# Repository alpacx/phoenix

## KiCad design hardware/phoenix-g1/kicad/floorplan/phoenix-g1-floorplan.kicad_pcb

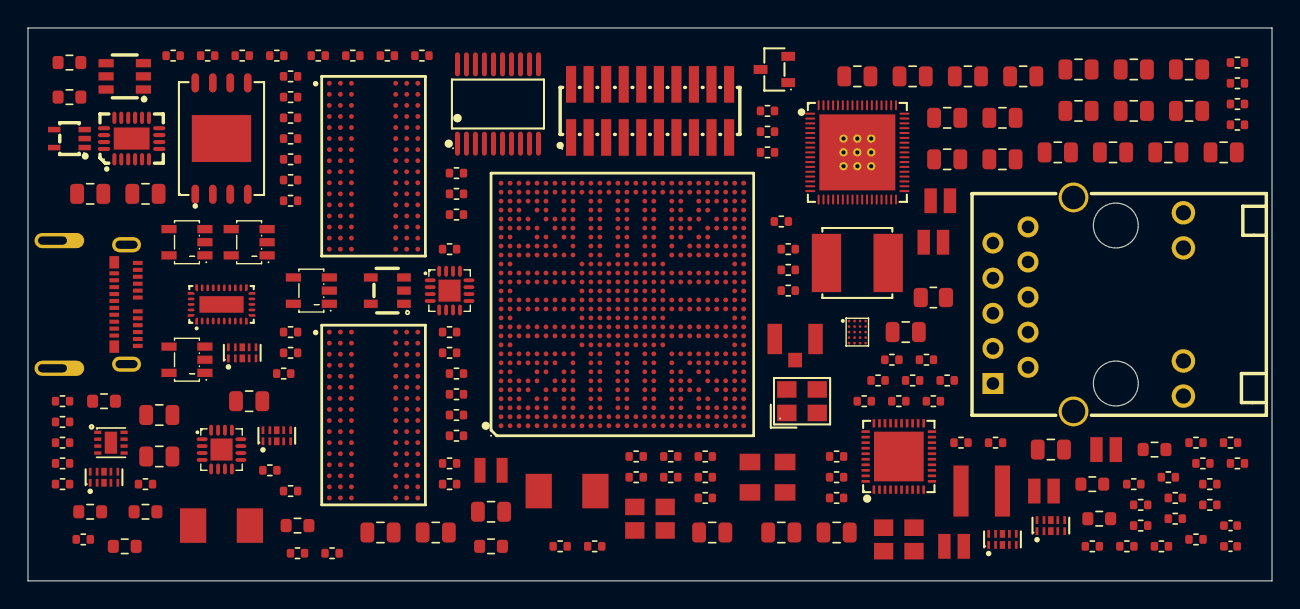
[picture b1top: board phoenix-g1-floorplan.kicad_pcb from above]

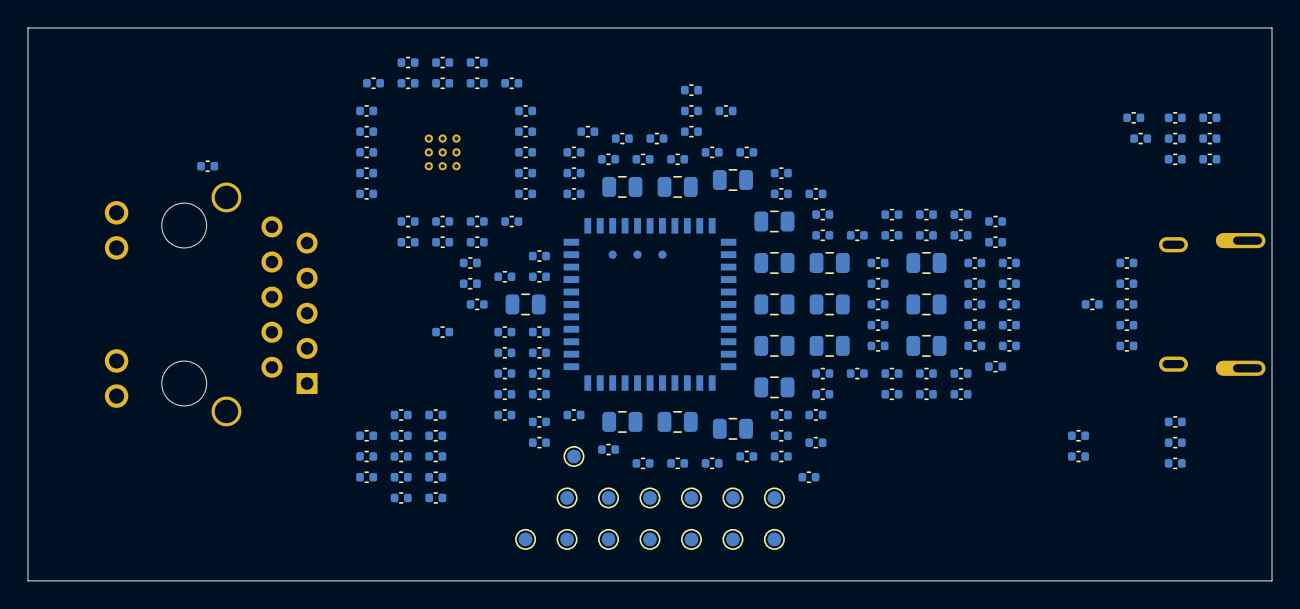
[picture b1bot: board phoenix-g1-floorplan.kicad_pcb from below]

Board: 6 copper layers, 90.0 x 40.0 mm, 354 parts (175 on the bottom side), 272 nets, no tracks yet.

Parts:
C401, C402, C1903: 1n / C0G; C_0402_1005Metric
C410, C411, C412, C451, C452, C454, C501, C512, C513, C514, C516, C517, C518, C522, C1103, C1104, C1105, C1106, C1107, C1401, C1503, C1811, C2007: 100n; C_0402_1005Metric
C413, C414, C415, C519, C1402: 1u; C_0402_1005Metric
C421, C422, C423, C424, C425, C431, C432, C433, C434, C435, C441, C442, C443, C444, C445, C1304, C1305, C1603, C1604, C1605, C1606, C1607, C1608, C1613, C1614, C1618, C1619, C1622, C1623, C2204: 22u / 10V; C_0805_2012Metric
C460, C461, C462, C463, C464, C465, C466, C467, C468, C469, C480, C481, C482, C483, C484, C485, C531, C1101, C1201, C1203, C1611, C1612, C1626, C1628, C1630, C1632, C1634, C1636, C1680, C1682, C1801, C1812, C2005: 1u / 10V; C_0402_1005Metric
C470, C1301, C1615, C1620, C1624, C1650, C1664, C1678, C2201: 10u / 10V; C_0805_2012Metric
C511, C515: 4.7u; C_0402_1005Metric
C520, C521, C1501, C1502: 20p C0G / tune; C_0402_1005Metric
C601, C602, C603, C604, C605: 100n / 16V X7R; C_0402_1005Metric
C606: 100n / 10V X7R; C_0402_1005Metric
C1001, C1002, C1011, C1012, C1013, C1014: 22u / 10V X5R; C_0805_2012Metric
C1020: 1u / 10V X5R; C_0402_1005Metric
C1102, C1802: 2.2u / 10V; C_0402_1005Metric
C1202: 22n / 10V; C_0402_1005Metric
C1302, C1601, C1609, C1616, C1621, C1625, C1627, C1629, C1631, C1633, C1635, C1637, C1638, C1639, C1640, C1641, C1642, C1643, C1644, C1645, C1646, C1647, C1651, C1652, C1653, C1654, C1655, C1656, C1657, C1658, C1659, C1660, C1661, C1662, C1665, C1666, C1667, C1668, C1669, C1670, C1671, C1672, C1673, C1674, C1675, C1676, C1679, C1681, C1683: 100n / 10V; C_0402_1005Metric
C1303: 10n / 10V; C_0402_1005Metric
C1602, C1610, C1617, C1648, C1649, C1663, C1677: 4.7u / 10V; C_0402_1005Metric
C1901, C1902: 1u / 25V X7R; C_0805_2012Metric
C2001: 22u / 6.3V; C_0805_2012Metric
C2002, C2006, C2202: 100n / 16V; C_0402_1005Metric
C2003: 4.7u / 6.3V; C_0805_2012Metric
C2004: 4.7u / 6.3V; C_0402_1005Metric
C2008, C2009: 8p C0G; C_0402_1005Metric
C2203: 1n / 10V; C_0402_1005Metric
FB2001: 100R @100MHz / 4A; R_0805_2012Metric
J1: 2012670005; USB_C_Molex_2012670005
J2: HR911130A; RJ45-TH_HR911130A
J3: PZ127-2-10-S; HDR-SMD_PZ127-2-10-S
J2001: U.FL-R-SMT-1; Hirose_UFL_R_SMT_1_80
L401, L402, L403, L404, L405: 470nH; L_APH201610
L501: 2.2uH DCR39m max; L_ANR4030
L1001: 240nH - candidate; IND-SMD_L5.0-W5.0-PRS5020-330MT
L1301, L2201: 2.2uH DCR35m max; L_APH0518
L2001: 2.2uH / 2.4A Isat at 20C; Murata_DFE201610E
Q1: MMBT3904-C20526; SOT-23-3_L2.9-W1.3-P1.90-LS2.4-BR
R201, R301: 240R 1%; R_0402_1005Metric
R401, R402: 1k 1%; R_0402_1005Metric
R410: 180k 1%; R_0402_1005Metric
R411, R1505, R2203: 100k 1%; R_0402_1005Metric
R412, R413, R516, R1402, R1403, R1404, R1405, R1504, R2002: 10k; R_0402_1005Metric
R414, R415, R501, R502, R503, R504, R505, R506, R507, R508, R509, R510, R511, R512, R515, R1401, R1501, R2003: 22R; R_0402_1005Metric
R416, R417: 2.2k; R_0402_1005Metric
R421, R422, R424, R2004: 100R; R_0402_1005Metric
R431: 105k 0.1%; R_0603_1608Metric
R432: 120k 0.1%; R_0603_1608Metric
R513: 2.49k 1%; R_0402_1005Metric
R514: 1.8k; R_0402_1005Metric
R521, R522, R523, R524, R525, R526, R527, R528, R529, R2101, R2102: 4.7k; R_0402_1005Metric
R530: 0R - power link; R_0402_1005Metric
R601, R605, R606: 300k 0.1% 25ppm; R_0603_1608Metric
R602, R603, R604: 200k 1%; R_0402_1005Metric
R1001: 100R 1%; R_0402_1005Metric
R1002: 51k 1%; R_0402_1005Metric
R1101, R1103, R1202, R1301, R1804, R2201: 100k; R_0402_1005Metric
R1102, R1802, R1811, R1812, R1813, R1814, R1815, R2010, R2011, R2012, R2013, R2014, R2103, R2104: 47k; R_0402_1005Metric
R1201: 806R 1%; R_0603_1608Metric
R1502: 1M; R_0402_1005Metric
R1503: 120R 1%; R_0402_1005Metric
R1506: 1M 1%; R_0402_1005Metric
R1507: 0R; R_0402_1005Metric
R1601, R1602: 0R supply link; R_0402_1005Metric
R1801: 1k; R_0402_1005Metric
R1803: 180R 1%; R_0603_1608Metric
R1901: 35.7k 0.1% 25ppm; R_0603_1608Metric
R1902, R1904: 10k 0.1% 25ppm; R_0402_1005Metric
R1903: 47.5k 0.1% 25ppm; R_0603_1608Metric
R1905: 33.2k 1%; R_0603_1608Metric
R2001: 0R RF tuning; R_0402_1005Metric
R2202: 348k 1%; R_0603_1608Metric
TP1: GND; TestPoint_Pad_D1.0mm
TP2: VBUS_RAW; TestPoint_Pad_D1.0mm
TP3: +5V_MAIN; TestPoint_Pad_D1.0mm
TP4: +3V3_SYS; TestPoint_Pad_D1.0mm
TP5: +3V3_PMU; TestPoint_Pad_D1.0mm
TP6: +3V3_IO; TestPoint_Pad_D1.0mm
TP7: +1V5_DDR; TestPoint_Pad_D1.0mm
TP8: VDD_CPU; TestPoint_Pad_D1.0mm
TP9: RESET_N; TestPoint_Pad_D1.0mm
TP10: RECOVERY_ADC; TestPoint_Pad_D1.0mm
TP11: DEBUG_RX; TestPoint_Pad_D1.0mm
TP12: DEBUG_TX; TestPoint_Pad_D1.0mm
TP13: USB_POWER_FAULT_N; TestPoint_Pad_D1.0mm
TP14: SYS_3V3_PG; TestPoint_Pad_D1.0mm
U1: RK3568; BGA-636_L19.0-W19.0-P0.65-BL
U2, U3: H5TQ2G63GFR-TEC; TFBGA-96_L13.0-W7.5-R16-C6-P0.80-TL
U4: RK809-5; QFN-68_L7.0-W7.0-P0.35-BL-EP5.5
U5: RTL8211F-CG; WQFN-40_L5.0-W5.0-P0.4-BL-EP
U6: HD3SS3220IRNHR; WQFN-30_L4.5-W2.5-P0.4-BL-EP
U7, U8, U9: TPD4EUSB30DQAR; USON-10_L2.5-W1.0-P0.50-BL
U10: RK860-0; WLCSP-20_L2.0-W1.6-R5-C4-P0.40-TL
U11: TLV75533PDBVR; SOT-23-5_L3.0-W1.7-P0.95-LS2.8-BR
U12: TPS3808G33DBVR; SOT-23-6_L2.9-W1.6-P0.95-LS2.8-BR
U13, U16: SN74LVC1G04DBVR; SOT-23-5_L3.0-W1.7-P0.95-LS2.8-BR
U14: SN74LVC1G02DCKR; SC-70-5_L2.1-W1.3-P0.65-LS2.1-BR
U15: TPS259531DSGR; WSON-8_L2.0-W2.0-P0.50-TL-EP
U17: TPS62132RGTR; VQFN-16_L3.0-W3.0-P0.50-TL-EP
U18: W25Q256JVEIQTR; WSON-8_L8.0-W6.10-P1.27-BL-EP
U19: SN74LVC1G08DBVR; SOT-23-5_L3.0-W1.7-P0.95-LS2.8-BR
U20: TPS7A2030PDBVR; TSOT-23-5_L2.9-W1.6-P0.95-LS2.8-BR
U21: SN74LVC541APWR_C113281; TSSOP-20_L6.5-W4.4-P0.65-LS6.4-BL
U22, U23: TPD4E05U06DQAR; USON-10_L2.5-W1.0-P0.50-BL
U24: TPS25940ARVCR; WQFN-20_L4.0-W3.0-P0.50-BL-EP
U25: AP6256; AP6256_12x12_P0.9
U26: TPS62130RGTR; VQFN-16_L3.0-W3.0-P0.50-TL-EP
Y1: 24MHz CL12pF ESR40R; Crystal_3225_JWT
Y501: 25MHz CL12pF; Crystal_3225_YXC
Y2001: OVETDLJANF-32.768KHZ; Taitien_OV_5032
Y2002: X1E0000210877; CRYSTAL-SMD_4P-L3.2-W2.5-BL

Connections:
+1V0_PHY: C511.1, C512.1, C513.1, C514.1, C522.1, L501.2, U5.3, U5.8, U5.21, U5.38
+1V5_DDR: C433.1, C443.1, C1646.1, C1647.1, C1648.1, C1649.1, C1650.1, C1651.1, C1652.1, C1653.1, C1654.1, C1655.1, C1656.1, C1657.1, C1658.1, C1659.1, C1660.1, C1661.1, C1662.1, C1663.1, C1664.1, C1665.1, C1666.1, C1667.1, C1668.1, C1669.1, C1670.1, C1671.1, C1672.1, C1673.1, C1674.1, C1675.1, C1676.1, C1677.1, C1678.1, L403.2, R401.1, R431.1, TP7.1, U1.H9, U1.H11, U1.H12, U1.H14, U1.H15, U1.J9, U1.J11, U1.J12, U1.J14, U1.K10, U1.L9, U1.L10, U1.M9, U1.M10, U2.A1, U2.A8, U2.B2, U2.C1, U2.C9, U2.D2, U2.D9, U2.E9, U2.F1, U2.G7, U2.H2, U2.H9, U2.K2, U2.K8, U2.N1, U2.N9, U2.R1, U2.R9, U3.A1, U3.A8, U3.B2, U3.C1, U3.C9, U3.D2, U3.D9, U3.E9, U3.F1, U3.G7, U3.H2, U3.H9, U3.K2, U3.K8, U3.N1, U3.N9, U3.R1, U3.R9, U4.26
+1V8_SYS: C435.1, C445.1, L405.2, U4.59
+3V0_LCD: C1802.1, C1811.1, C1812.1, U20.5, U21.20
+3V3_AON: C606.1, C1102.1, C1103.1, C1104.1, C1105.1, C1106.1, C1107.1, R602.1, R603.1, R604.1, R1101.1, R1202.2, U6.8, U11.5, U12.3, U12.5, U12.6, U13.5, U14.5, U16.5, U19.5
+3V3_IO: C470.1, C1401.1, C1402.1, C1627.1, C1628.1, C1637.1, C1638.1, C1639.1, C1640.1, C1641.1, C1683.1, C2004.1, C2005.1, C2006.1, C2007.1, J3.1, R530.1, R1402.2, R1403.2, R1404.2, R1505.1, R1804.1, R1815.2, R2010.2, R2011.2, R2012.2, R2013.2, R2014.2, R2101.2, R2102.2, TP6.1, U1.H18, U1.J21, U1.L22, U1.M23, U1.R9, U1.U9, U4.55, U18.8, U20.3, U25.22, Y2001.1, Y2001.4
+3V3_PHY: C515.1, C516.1, C517.1, C518.1, C519.1, R514.2, R521.2, R525.2, R526.2, R527.2, R530.2, U5.11, U5.28, U5.29, U5.40
+3V3_PMU: C465.1, C1625.1, C1626.1, R412.1, R413.1, R416.1, R417.1, R1002.1, R2103.2, R2104.2, TP5.1, U1.W19, U1.Y20, U4.31
+3V3_SD: C469.1, U4.58
+3V3_SYS: C421.1, C422.1, C423.1, C424.1, C425.1, C480.1, C481.1, C482.1, C483.1, C484.1, C485.1, C1304.1, C1305.1, L1301.2, R410.1, R1301.2, TP4.1, U4.4, U4.10, U4.11, U4.22, U4.24, U4.30, U4.33, U4.45, U4.54, U4.57, U4.66, U17.14
+3V58_WIFI: C2204.1, FB2001.1, L2201.2, R2201.2, R2202.1, U26.14
+5V_MAIN: C1001.1, C1002.1, C1203.1, C1301.1, C1302.1, C1801.1, C2201.1, C2202.1, J3.2, R1803.1, TP3.1, U10.D1, U10.D2, U10.E1, U10.E2, U15.5, U17.10, U17.11, U17.12, U20.1, U26.10, U26.11, U26.12, U26.13
AON_READY: R1101.2, U12.1, U13.2, U19.2
CC_OUT1_N: R603.2, U6.25, U14.1
CC_OUT2_N: R604.2, U6.26, U14.2
CC_VBUS_SENSE: R606.2, U6.5
CC_VBUS_SERIES_1: R601.2, R605.1
CC_VBUS_SERIES_2: R605.2, R606.1
CHASSIS: J2.P10, J2.SHIELD0, J2.SHIELD1
CPU_BUCK_EN: R1002.2, U10.A2
CPU_SW: L1001.1, U10.D3, U10.D4, U10.E3, U10.E4
DDR3_A0: U1.E4, U2.N3, U3.N3
DDR3_A1: U1.E11, U2.P7, U3.P7
DDR3_A2: U1.F5, U2.P3, U3.P3
DDR3_A3: U1.F4, U2.N2, U3.N2
DDR3_A4: U1.B1, U2.P8, U3.P8
DDR3_A5: U1.A5, U2.P2, U3.P2
DDR3_A6: U1.C1, U2.R8, U3.R8
DDR3_A7: U1.C2, U2.R2, U3.R2
DDR3_A8: U1.A8, U2.T8, U3.T8
DDR3_A9: U1.B6, U2.R3, U3.R3
DDR3_A10: U1.D6, U2.L7, U3.L7
DDR3_A11: U1.B7, U2.R7, U3.R7
DDR3_A12: U1.E9, U2.N7, U3.N7
DDR3_A13: U1.A7, U2.T3, U3.T3
DDR3_BA0: U1.F7, U2.M2, U3.M2
DDR3_BA1: U1.D9, U2.N8, U3.N8
DDR3_BA2: U1.C4, U2.M3, U3.M3
DDR3_CASN: U1.E6, U2.K3, U3.K3
DDR3_CKE: U1.B3, U2.K9, U3.K9
DDR3_CLKN: U1.A4, U2.K7, U3.K7
DDR3_CLKP: U1.B4, U2.J7, U3.J7
DDR3_CS0N: U1.D8, U2.L2, U3.L2
DDR3_DM0: U1.H5, U2.E7
DDR3_DM1: U1.J4, U2.D3
DDR3_DM2: U1.D14, U3.E7
DDR3_DM3: U1.E17, U3.D3
DDR3_DQ0: U1.F2, U2.E3
DDR3_DQ1: U1.E1, U2.F7
DDR3_DQ2: U1.E2, U2.F2
DDR3_DQ3: U1.D1, U2.F8
DDR3_DQ4: U1.J1, U2.H3
DDR3_DQ5: U1.J2, U2.H8
DDR3_DQ6: U1.H1, U2.G2
DDR3_DQ7: U1.H4, U2.H7
DDR3_DQ8: U1.M1, U2.D7
DDR3_DQ9: U1.N2, U2.C3
DDR3_DQ10: U1.L7, U2.C8
DDR3_DQ11: U1.L6, U2.C2
DDR3_DQ12: U1.K2, U2.A7
DDR3_DQ13: U1.J6, U2.A2
DDR3_DQ14: U1.J7, U2.B8
DDR3_DQ15: U1.L4, U2.A3
DDR3_DQ16: U1.B10, U3.E3
DDR3_DQ17: U1.A9, U3.F7
DDR3_DQ18: U1.D12, U3.F2
DDR3_DQ19: U1.E12, U3.F8
DDR3_DQ20: U1.A12, U3.H3
DDR3_DQ21: U1.D15, U3.H8
DDR3_DQ22: U1.E15, U3.G2
DDR3_DQ23: U1.E14, U3.H7
DDR3_DQ24: U1.A16, U3.D7
DDR3_DQ25: U1.B17, U3.C3
DDR3_DQ26: U1.A17, U3.C8
DDR3_DQ27: U1.B18, U3.C2
DDR3_DQ28: U1.B13, U3.A7
DDR3_DQ29: U1.A13, U3.A2
DDR3_DQ30: U1.D17, U3.B8
DDR3_DQ31: U1.B14, U3.A3
DDR3_DQS0N: U1.G2, U2.G3
DDR3_DQS0P: U1.G1, U2.F3
DDR3_DQS1N: U1.L1, U2.B7
DDR3_DQS1P: U1.L2, U2.C7
DDR3_DQS2N: U1.B11, U3.G3
DDR3_DQS2P: U1.A11, U3.F3
DDR3_DQS3N: U1.A15, U3.B7
DDR3_DQS3P: U1.B15, U3.C7
DDR3_ODT0: U1.E8, U2.K1, U3.K1
DDR3_RASN: U1.D5, U2.J3, U3.J3
DDR3_RESETN: U1.F11, U2.T2, U3.T2
DDR3_WEN: U1.F8, U2.L3, U3.L3
DDR_FB: R431.2, R432.1, U4.27
DDR_RZQ: R1503.1, U1.H7
DDR_VREFCA: C401.1, R401.2, R402.1, U2.M8, U3.M8
DDR_VREFDQ: C402.1, U1.P8, U2.H1, U3.H1
DEBUG_RX: TP11.1, U1.AC20
DEBUG_TX: TP12.1, U1.AH24
ETH_CENTER_TAP: C531.1, J2.P1
ETH_MDC: U1.U5, U5.13
ETH_MDI0_N: J2.P3, U5.2, U22.2
ETH_MDI0_P: J2.P2, U5.1, U22.1
ETH_MDI1_N: J2.P7, U5.5, U22.5
ETH_MDI1_P: J2.P4, U5.4, U22.4
ETH_MDI2_N: J2.P6, U5.7, U23.2
ETH_MDI2_P: J2.P5, U5.6, U23.1
ETH_MDI3_N: J2.P9, U5.10, U23.5
ETH_MDI3_P: J2.P8, U5.9, U23.4
ETH_MDIO: R514.1, U1.U4, U5.14
ETH_RESET_GPIO_N: R515.1, U1.AE26
ETH_RXCLK: R512.1, U1.Y3
ETH_RXD0: R507.1, U1.W1
ETH_RXD1: R508.1, U1.V7
ETH_RXD2: R509.1, U1.AA2
ETH_RXD3: R510.1, U1.Y4
ETH_RXDV_CRS: R511.1, U1.V2
ETH_TXCLK: R506.1, U1.AA3
ETH_TXD0: R501.1, U1.Y2
ETH_TXD1: R502.1, U1.Y1
ETH_TXD2: R503.1, U1.Y6
ETH_TXD3: R504.1, U1.Y5
ETH_TXEN: R505.1, U1.W2
EXP_GPIO0: J3.12, U1.F27
EXP_GPIO1: J3.14, U1.U2
EXP_GPIO2: J3.16, U1.V4
EXP_GPIO3: J3.18, U1.V1
EXP_I2C_SCL: J3.5, R2102.1, U1.V5
EXP_I2C_SDA: J3.3, R2101.1, U1.V6
EXP_SPI_CLK: J3.7, U1.AC22
EXP_SPI_CS0_N: J3.13, R2103.1, U1.AD20
EXP_SPI_CS1_N: J3.15, R2104.1, U1.AD21
EXP_SPI_MISO: J3.11, U1.AC21
EXP_SPI_MOSI: J3.9, U1.AA20
EXP_UART_RX: J3.19, U1.F28
EXP_UART_TX: J3.17, U1.G27
FLASH_CLK: R1401.2, U18.6
FLASH_VOL_SEL: R1405.1, U1.AG25
FSPI_CLK: R1401.1, U1.A22
FSPI_CS_N: R1402.1, U1.C23, U18.1
FSPI_D0: U1.C24, U18.5
FSPI_D1: U1.D23, U18.2
FSPI_D2: R1403.1, U1.F20, U18.3
FSPI_D3: R1404.1, U1.A27, U18.7
GND: C401.2, C402.2, C410.2, C411.2, C412.2, C413.2, C414.2, C415.2, C421.2, C422.2, C423.2, C424.2, C425.2, C431.2, C432.2, C433.2, C434.2, C435.2, C441.2, C442.2, C443.2, C444.2, C445.2, C460.2, C461.2, C462.2, C463.2, C464.2, C465.2, C466.2, C467.2, C468.2, C469.2, C470.2, C480.2, C481.2, C482.2, C483.2, C484.2, C485.2, C501.2, C511.2, C512.2, C513.2, C514.2, C515.2, C516.2, C517.2, C518.2, C519.2, C520.2, C521.2, C522.2, C531.2, C605.2, C606.2, C1001.2, C1002.2, C1011.2, C1012.2, C1013.2, C1014.2, C1101.2, C1102.2, C1103.2, C1104.2, C1105.2, C1106.2, C1107.2, C1201.2, C1202.2, C1203.2, C1301.2, C1302.2, C1303.2, C1304.2, C1305.2, C1401.2, C1402.2, C1501.2, C1502.2, C1503.2, C1601.2, C1602.2, C1603.2, C1604.2, C1605.2, C1606.2, C1607.2, C1608.2, C1609.2, C1610.2, C1611.2, C1612.2, C1613.2, C1614.2, C1615.2, C1616.2, C1617.2, C1618.2, C1619.2, C1620.2, C1621.2, C1622.2, C1623.2, C1624.2, C1625.2, C1626.2, C1627.2, C1628.2, C1629.2, C1630.2, C1631.2, C1632.2, C1633.2, C1634.2, C1635.2, C1636.2, C1637.2, C1638.2, C1639.2, C1640.2, C1641.2, C1642.2, C1643.2, C1644.2, C1645.2, C1646.2, C1647.2, C1648.2, C1649.2, C1650.2, C1651.2, C1652.2, C1653.2, C1654.2, C1655.2, C1656.2, C1657.2, C1658.2, C1659.2, C1660.2, C1661.2, C1662.2, C1663.2, C1664.2, C1665.2, C1666.2, C1667.2, C1668.2, C1669.2, C1670.2, C1671.2, C1672.2, C1673.2, C1674.2, C1675.2, C1676.2, C1677.2, C1678.2, C1679.2, C1680.2, C1681.2, C1682.2, C1683.2, C1801.2, C1802.2, C1811.2, C1812.2, C1901.2, C1902.2, C1903.2, C2001.2, C2002.2, C2003.2, C2004.2, C2005.2, C2006.2, C2007.2, C2008.2, C2009.2, C2201.2, C2202.2, C2203.2, C2204.2, J1.A1, J1.A12, J1.B1, J1.B12, J3.4, J3.6, J3.8, J3.10, J3.20, J2001.2, J2001.3, Q1.2, R201.2, R301.2, R402.2, R411.2, R432.2, R513.2, R516.2, R522.2, R523.2, R524.2, R528.2, R529.2, R1102.2, R1103.2, R1201.2, R1405.2, R1503.2, R1506.2, R1802.2, R1804.2, R1811.2, R1812.2, R1813.2, R1814.2, R1902.2, R1904.2, R1905.2, R2002.2, R2203.2, TP1.1, U1.A1, U1.A3, U1.A6, U1.A10, U1.A14, U1.A18, U1.A28, U1.AA4, U1.AA9, U1.AA12, U1.AA14, U1.AA15, U1.AA17, U1.AA23, U1.AA24, U1.AA25, U1.AA26, U1.AB2, U1.AB6, U1.AB11, U1.AB12, U1.AB14, U1.AB15, U1.AB17, U1.AB24, U1.AC9, U1.AC11, U1.AC12, U1.AC15, U1.AC18, U1.AC25, U1.AC26, U1.AD3, U1.AD26, U1.AE6, U1.AE14, U1.AE17, U1.AE20, U1.AE21, U1.AE27, U1.AE28, U1.AF3, U1.AF9, U1.AF11, U1.AF12, U1.AF14, U1.AF15, U1.AF17, U1.AF18, U1.AF20, U1.AF21, U1.AF26, U1.AG5, U1.AG18, U1.AH1, U1.AH8, U1.AH18, U1.AH23, U1.AH28, U1.B5, U1.B9, U1.B12, U1.B16, U1.B23, U1.B26, U1.C3, U1.C6, U1.C8, U1.C9, U1.C11, U1.C12, U1.C14, U1.C15, U1.C17, U1.C18, U1.C25, U1.D2, U1.D3, U1.D11, U1.D28, U1.E3, U1.E7, U1.F1, U1.F3, U1.F9, U1.F12, U1.F14, U1.F15, U1.F17, U1.G5, U1.G6, U1.G8, U1.G9, U1.G11, U1.G12, U1.G14, U1.G15, U1.G17, U1.G18, U1.G24, U1.H2, U1.H3, U1.H6, U1.J3, U1.J5, U1.J8, U1.J17, U1.J18, U1.J20, U1.J22, U1.J26, U1.J27, U1.K1, U1.K11, U1.K12, U1.K13, U1.K14, U1.K19, U1.L3, U1.L5, U1.L8, U1.L11, U1.L13, U1.L14, U1.L19, U1.L20, U1.L21, U1.L24, U1.L26, U1.M2, U1.M3, U1.M6, U1.M8, U1.M11, U1.M13, U1.M14, U1.M16, U1.M18, U1.M20, U1.M21, U1.M22, U1.M26, U1.N1, U1.N11, U1.N12, U1.N14, U1.N15, U1.N17, U1.N18, U1.N28, U1.P3, U1.P6, U1.P9, U1.P10, U1.P12, U1.P14, U1.P15, U1.P17, U1.P21, U1.P26, U1.R3, U1.R6, U1.R8, U1.R10, U1.R11, U1.R14, U1.R15, U1.R17, U1.R18, U1.R19, U1.R23, U1.R26, U1.T10, U1.T11, U1.T14, U1.T15, U1.T17, U1.T18, U1.T19, U1.U1, U1.U6, U1.U7, U1.U8, U1.U10, U1.U14, U1.U15, U1.U16, U1.U17, U1.U18, U1.U20, U1.U21, U1.U22, U1.U23, U1.U26, U1.V3, U1.V8, U1.V9, U1.V13, U1.V14, U1.V15, U1.V16, U1.V17, U1.V18, U1.V20, U1.V22, U1.V23, U1.V26, U1.W10, U1.W11, U1.W12, U1.W13, U1.W14, U1.W15, U1.W16, U1.W17, U1.W18, U1.Y8, U1.Y9, U1.Y11, U1.Y12, U1.Y14, U1.Y15, U1.Y17, U1.Y18, U1.Y23, U1.Y24, U1.Y25, U1.Y26, U2.A9, U2.B1, U2.B3, U2.B9, U2.D1, U2.D8, U2.E1, U2.E2, U2.E8, U2.F9, U2.G1, U2.G8, U2.G9, U2.J2, U2.J8, U2.M1, U2.M9, U2.P1, U2.P9, U2.T1, U2.T9, U3.A9, U3.B1, U3.B3, U3.B9, U3.D1, U3.D8, U3.E1, U3.E2, U3.E8, U3.F9, U3.G1, U3.G8, U3.G9, U3.J2, U3.J8, U3.M1, U3.M9, U3.P1, U3.P9, U3.T1, U3.T9, U4.14, U4.15, U4.16, U4.17, U4.19, U4.40, U4.47, U4.56, U4.62, U4.63, U4.69, U5.41, U6.3, U6.4, U6.13, U6.28, U6.31, U7.3, U7.8, U8.3, U8.8, U9.3, U9.8, U10.B2, U10.B3, U10.B4, U10.C1, U10.C2, U10.C3, U10.C4, U11.2, U12.2, U13.3, U14.3, U15.8, U15.9, U16.3, U17.5, U17.6, U17.7, U17.8, U17.15, U17.16, U17.17, U18.4, U18.9, U19.3, U20.2, U21.1, U21.7, U21.8, U21.9, U21.10, U21.19, U22.3, U22.8, U23.3, U23.8, U24.1, U24.3, U24.16, U24.21, U25.1, U25.3, U25.6, U25.20, U25.26, U25.27, U25.28, U25.29, U25.31, U25.33, U25.34, U25.36, U25.43, U25.44, U26.6, U26.7, U26.8, U26.15, U26.16, U26.17, Y1.2, Y1.4, Y501.2, Y501.4, Y2001.2, Y2002.2, Y2002.4
I2C0_SCL: R414.1, R416.2, U1.AF24, U10.A3
I2C0_SDA: R415.1, R417.2, U1.AB21, U10.B1
LCD_BL_BASE: Q1.1, R1801.2, R1802.1
LCD_BL_PWM: R1801.1, U1.AE23
LCD_CS_N: R1815.1, U1.F24, U21.6
LCD_DC: R1813.1, U1.H23, U21.4
LCD_MOSI: R1811.1, U1.H25, U21.2
LCD_RESET_N: R1814.1, U1.F26, U21.5
LCD_SCLK: R1812.1, U1.G28, U21.3
MUX_TX1_N: C602.1, U6.16
MUX_TX1_P: C601.1, U6.17
MUX_TX2_N: C604.1, U6.20
MUX_TX2_P: C603.1, U6.21
PHY_CFG_EXT: R527.1, U5.32
PHY_CFG_LDO0: R528.1, U5.33
PHY_CFG_LDO1: R529.1, U5.34
PHY_RESET_N: C501.1, R515.2, R516.1, U5.12
PHY_RSET: R513.1, U5.39
PHY_RXCLK: R512.2, R522.1, U5.27
PHY_RXD0: R507.2, R526.1, U5.25
PHY_RXD1: R508.2, R525.1, U5.24
PHY_RXD2: R509.2, R524.1, U5.23
PHY_RXD3: R510.2, R521.1, U5.22
PHY_RXDV_CRS: R511.2, R523.1, U5.26
PHY_SW: L501.1, U5.30
PHY_TXCLK: R506.2, U5.20
PHY_TXD0: R501.2, U5.18
PHY_TXD1: R502.2, U5.17
PHY_TXD2: R503.2, U5.16
PHY_TXD3: R504.2, U5.15
PHY_TXEN: R505.2, U5.19
PHY_XIN: C520.1, U5.36, Y501.1
PHY_XOUT: C521.1, U5.37, Y501.3
PMIC_1V8A: C414.1, U4.44
PMIC_1V8D: C415.1, U4.48
PMIC_INT_N: R413.2, U1.AA22, U4.7
PMIC_PWRON_N: C412.1, U4.52
PMIC_SCL: R414.2, U4.1
PMIC_SDA: R415.2, U4.2
PMIC_SLEEP: U1.AG28, U4.49, U10.A1
PMIC_SW1: L401.1, U4.12
PMIC_SW2: L402.1, U4.9
PMIC_SW3: L403.1, U4.25
PMIC_SW4: L404.1, U4.65
PMIC_SW5: L405.1, U4.53
PMIC_VDC: C410.1, R410.2, R411.1, U4.61
PMIC_VREF: C413.1, U4.46
RECOVERY_ADC: R1504.1, TP10.1, U1.B27
RESET_N: C411.1, R412.2, R1103.1, R1507.2, TP9.1, U1.AH27, U4.67, U16.2
SOC_USB_RX_N: U1.R27, U6.10
SOC_USB_RX_P: U1.R28, U6.9
SOC_USB_TX_N: U1.T27, U6.7
SOC_USB_TX_P: U1.T28, U6.6
SOC_VBUS_DET: C1503.1, R1505.2, R1506.1, U1.M24
SYS_3V3_PG: R1301.1, TP14.1, U17.4
SYS_SS: C1303.1, U17.9
SYS_SW: L1301.1, U17.1, U17.2, U17.3
THERMAL_SHUTDOWN: R1507.1, U1.AG26
U2_ZQ_240R_TO_GND: R201.1, U2.L8
U3_ZQ_240R_TO_GND: R301.1, U3.L8
USB_AVDD_0V9: C1679.1, C1680.1, R1601.2, U1.P22
USB_AVDD_1V8: C1681.1, C1682.1, R1602.2, U1.P23
USB_CC1: J1.A5, U6.2, U9.4
USB_CC2: J1.B5, U6.1, U9.5
USB_CC_ENABLE_N: U6.29, U13.4
USB_CURRENT_OK: U14.4, U19.1
USB_DM: J1.A7, J1.B7, U1.P28, U9.2
USB_DP: J1.A6, J1.B6, U1.P27, U9.1
USB_DVDT: C1202.1, U15.1
USB_ILIM: R1201.1, U15.7
USB_MAIN_ENABLE: R1102.1, U15.2, U19.4
USB_MUX_ENABLE_N: U6.12, U16.4
USB_ORIENTATION: R602.2, U6.11
USB_POWER_FAULT_N: R1202.1, TP13.1, U15.6
USB_RX1_N: J1.B10, U6.14, U7.5
USB_RX1_P: J1.B11, U6.15, U7.4
USB_RX2_N: J1.A10, U6.18, U8.5
USB_RX2_P: J1.A11, U6.19, U8.4
USB_TX1_N: C602.2, J1.A3, U7.2
USB_TX1_P: C601.2, J1.A2, U7.1
USB_TX2_N: C604.2, J1.B3, U8.2
USB_TX2_P: C603.2, J1.B2, U8.1
VBUS_GUARD_DVDT: C1903.1, U24.18
VBUS_GUARD_ILIM: R1905.1, U24.17
VBUS_OVP: R1903.2, R1904.1, U24.15
VBUS_PROTECTED: C605.1, C1101.1, C1201.1, C1902.1, R601.1, U6.30, U11.1, U11.3, U15.3, U15.4, U24.4, U24.5, U24.6, U24.7, U24.8
VBUS_RAW: C1901.1, J1.A4, J1.A9, J1.B4, J1.B9, R1901.1, R1903.1, TP2.1, U24.9, U24.10, U24.11, U24.12, U24.13
VBUS_UVLO: R1901.2, R1902.1, U24.14
VCCA1V8_IMAGE: C468.1, U4.6
VCCA1V8_PMU: C467.1, C1631.1, C1632.1, U1.Y21, U4.5
VCCA_1V8: C466.1, C1635.1, C1636.1, C1644.1, C1645.1, R1504.2, R1602.1, U1.H20, U1.H22, U1.N10, U1.R22, U4.3
VCCIO_ACODEC: C463.1, U4.28
VCCIO_SD: C464.1, U4.29
VDDA0V9_IMAGE: C460.1, U4.23
VDDA0V9_PMU: C462.1, C1629.1, C1630.1, U1.V19, U1.V21, U4.20
VDDA_0V9: C461.1, C1633.1, C1634.1, C1642.1, C1643.1, R1601.1, U1.P11, U1.R20, U1.R21, U4.21
VDD_CPU: C1011.1, C1012.1, C1013.1, C1014.1, C1020.1, C1601.1, C1602.1, C1603.1, C1604.1, C1605.1, C1606.1, C1607.1, C1608.1, L1001.2, R1001.1, TP8.1, U1.J15, U1.K15, U1.K16, U1.K17, U1.K18, U1.L15, U1.L16, U1.L17, U1.L18, U1.M17
VDD_CPU_COM: C1020.2, R1001.2, U1.M15, U10.A4
VDD_GPU: C432.1, C442.1, C452.1, C1616.1, C1617.1, C1618.1, C1619.1, C1620.1, L402.2, R422.1, U1.R13, U1.T13, U1.U11, U1.U12, U1.U13
VDD_GPU_COM: C452.2, R422.2, U4.8
VDD_LOGIC: C431.1, C441.1, C451.1, C1609.1, C1610.1, C1611.1, C1612.1, C1613.1, C1614.1, C1615.1, L401.2, R421.1, U1.L12, U1.M12, U1.N13, U1.N16, U1.P13, U1.P16, U1.R12, U1.R16, U1.T12, U1.T16
VDD_LOGIC_COM: C451.2, R421.2, U4.13
VDD_NPU: C434.1, C444.1, C454.1, C1621.1, C1622.1, C1623.1, C1624.1, L404.2, R424.1, U1.M19, U1.N19, U1.P18, U1.P19, U1.P20
VDD_NPU_COM: C454.2, R424.2, U4.64
WIFI_ANT: J2001.1, R2001.2
WIFI_BUCK_OUT: C2003.1, L2001.2, U25.23
WIFI_BUCK_SW: L2001.1, U25.21
WIFI_CLK: U1.D27, U25.17
WIFI_CMD: R2014.1, U1.C28, U25.16
WIFI_D0: R2010.1, U1.E27, U25.18
WIFI_D1: R2011.1, U1.E28, U25.19
WIFI_D2: R2012.1, U1.B28, U25.14
WIFI_D3: R2013.1, U1.C27, U25.15
WIFI_HOST_WAKE: U1.E25, U25.13
WIFI_LPO: R2003.2, U25.24
WIFI_LPO_SRC: R2003.1, Y2001.3
WIFI_REG_ON: R2002.1, U1.D26, U25.12
WIFI_RF: R2001.1, U25.2
WIFI_VBAT: C2001.1, C2002.1, FB2001.2, U25.9
WIFI_VBAT_FB: R2202.2, R2203.1, U26.5
WIFI_VBAT_PG: R2201.1, U17.13, U26.4
WIFI_VBAT_SS: C2203.1, U26.9
WIFI_VBAT_SW: L2201.1, U26.1, U26.2, U26.3
WIFI_XIN: C2008.1, U25.10, Y2002.1
WIFI_XOUT: R2004.1, U25.11
WIFI_XTAL_OUT: C2009.1, R2004.2, Y2002.3
XIN24M: C1501.1, R1502.2, U1.AF28, Y1.1
XOUT24M: R1501.1, R1502.1, U1.AF27
XTAL24_DRIVE: C1502.1, R1501.2, Y1.3
